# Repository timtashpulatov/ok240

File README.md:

# ok240

https://svofski.github.io/pretty-8080-assembler/?https://raw.githubusercontent.com/timtashpulatov/ok240/master/graf.asm

https://svofski.github.io/pretty-8080-assembler/?https://raw.githubusercontent.com/timtashpulatov/ok240/master/ints.asm

https://svofski.github.io/pretty-8080-assembler/?https://raw.githubusercontent.com/timtashpulatov/ok240/master/tet.asm

https://svofski.github.io/pretty-8080-assembler/?https://raw.githubusercontent.com/timtashpulatov/ok240/master/ark.asm

https://svofski.github.io/pretty-8080-assembler/?https://raw.githubusercontent.com/timtashpulatov/ok240/master/hexload.asm

Literature:

<ul>
<li>https://tetris.fandom.com/wiki/Random_Generator
<li>https://zx-pk.ru/threads/23100-generator-psevdosluchajnykh-chisel/page5.html
<li>https://tetris.fandom.com/wiki/Scoring
<li>https://en.wikipedia.org/wiki/Bit_blit
</ul>

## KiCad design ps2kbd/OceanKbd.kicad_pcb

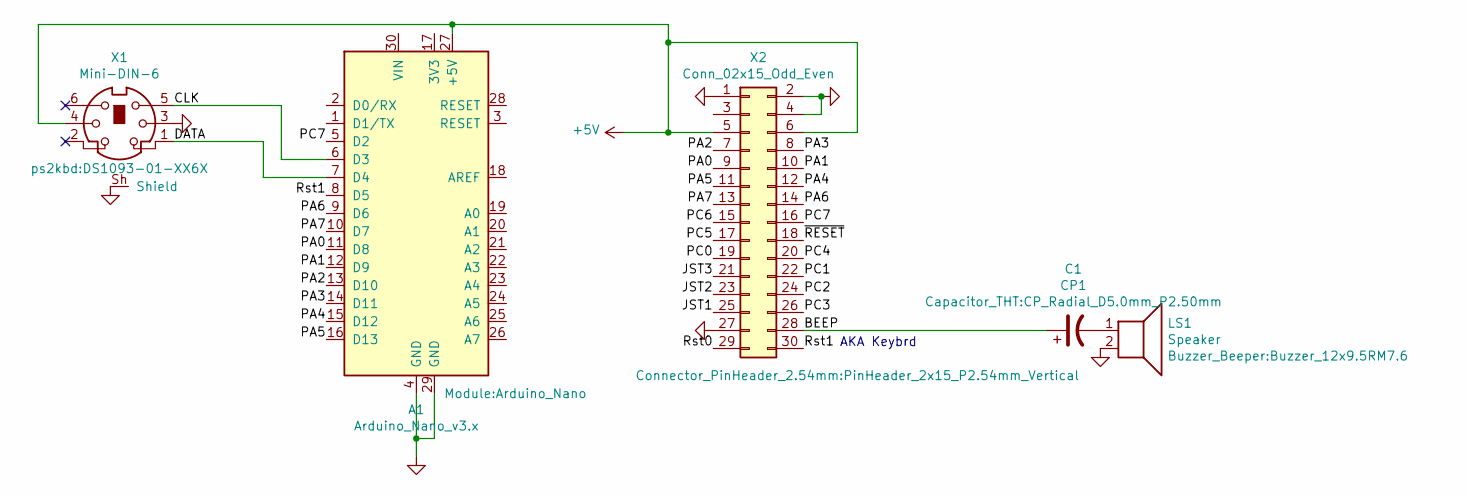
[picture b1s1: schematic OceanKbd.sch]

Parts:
A1: Arduino_Nano_v3.x; Arduino_Nano
C1: CP1; CP_Radial_D5.0mm_P2.50mm
LS1: Speaker; Buzzer_12x9.5RM7.6
X1: Mini-DIN-6; DS1093-01-XX6X
X2: Conn_02x15_Odd_Even; PinHeader_2x15_P2.54mm_Vertical

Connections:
+5V: A1.27 (+5V), X1.4, X2.5, X2.6
/BEEP: C1.1, X2.28
/CLK: A1.6 (D3), X1.5
/DATA: A1.7 (D4), X1.1
/JST1: X2.25
/JST2: X2.23
/JST3: X2.21
/PA0: A1.11 (D8), X2.9
/PA1: A1.12 (D9), X2.10
/PA2: A1.13 (D10), X2.7
/PA3: A1.14 (D11), X2.8
/PA4: A1.15 (D12), X2.12
/PA5: A1.16 (D13), X2.11
/PA6: A1.9 (D6), X2.14
/PA7: A1.10 (D7), X2.13
/PC0: X2.19
/PC1: X2.22
/PC2: X2.24
/PC3: X2.26
/PC4: X2.20
/PC5: X2.17
/PC6: X2.15
/PC7: A1.5 (D2), X2.16
/Rst0: X2.29
/Rst1: A1.8 (D5), X2.30
/~RESET: X2.18
GND: A1.4 (GND), A1.29 (GND), LS1.2, X1.3, X1.SH, X1.Sh (Shield), X2.1, X2.2, X2.4, X2.27
unnamed: C1.2, LS1.1

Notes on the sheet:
AKA Keybrd

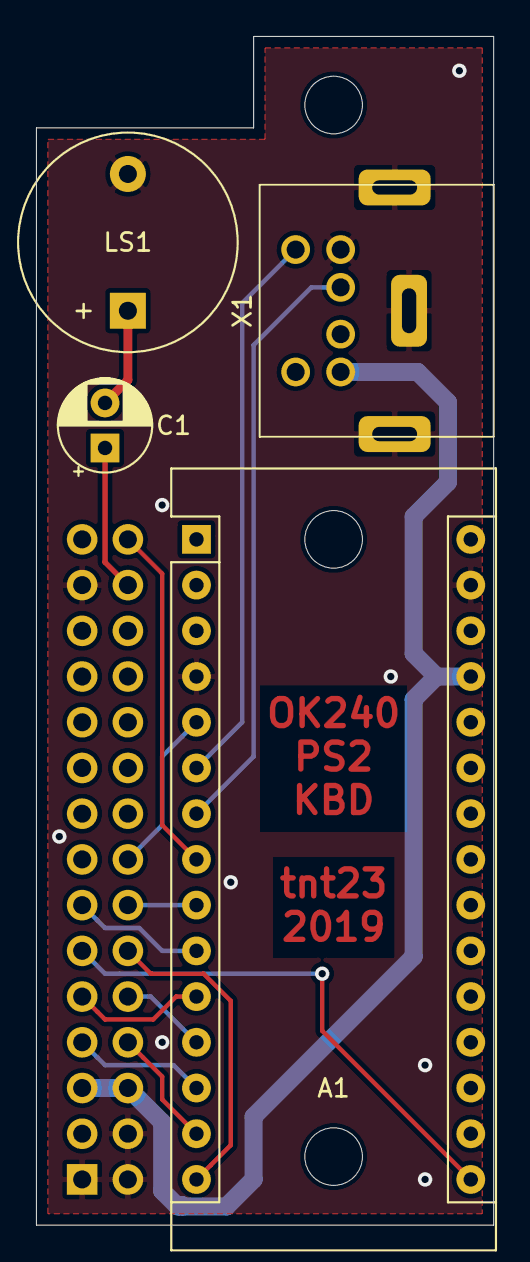
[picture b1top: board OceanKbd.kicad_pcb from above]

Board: 2 copper layers, 25.4 x 66.0 mm, 5 parts (1 on the bottom side), 16 nets.

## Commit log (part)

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2025-06-07 Add more cutouts to floppy frame
2025-06-08 More 3d stuff
2025-06-12 Another approach to bottom lid
2025-06-13 New top lid
2025-06-13 More Tops and drawings
2025-06-14 Update for top lid posts
2025-06-14 Add stringers to pillars
2025-06-18 Better Lid1 Part
2025-06-18 New BottomLid1
2025-06-18 More updates to bottom lid
2025-06-19 Simplified bottom with stands
2025-06-19 Redesign bottom and top halves
2025-06-20 Cleaned top and bottom lids
2025-06-20 Add floppy bracket
2025-06-20 Enhance side bracket with some chamfering
2025-06-21 Update side bracket, add mount posts to top lid
2025-06-21 Update assy
2025-06-27 Add lip to bottom lid
2025-06-27 PCB mount holes on lower lid
2025-07-01 Add floppy cutout
2025-07-02 New top and bottom parts with grooves
2025-07-11 Three locks added for bottom part
2025-07-12 Chamfer top alignment pads, add dowel pin for reference
2025-07-12 Use split halves as new Left and Right features
2025-07-12 Make lock pad two-dimentional and shift it for symmetry
2025-07-12 Add dowel holes to left half
2025-07-12 Shape dowel holes as drops for better printing and mirror them
2025-07-12 Teardrop dowel holes properly redone as features
2025-07-19 Add vents to Left bottom part
2025-07-20 Rename vents feature to Vents
2025-07-21 Add supporting lip
2025-07-22 Fix left vents
2025-07-25 Add 1mm chamfer to left bottom part, to reduce elephant foot etc
2025-07-25 Change bottom chamfer for 45 degrees, add 1mm fillets
2025-07-25 Add right angle IDC 30-pin connector 3D models
2025-07-25 Fix lip chamfer and fillets
2025-07-25 Add fillets to right bottom part
2025-07-26 Increase fillet radius to 1.5mm
2025-07-26 Increase fillet radius to 1.5mm for Left bottom part
2025-07-27 Add cutouts for power button and LED
2025-07-27 Up bottom part
2025-07-29 Add stand with heat insert for power switch
2025-07-29 Add right stand
2025-07-29 Power button
2025-07-29 Misc up
2025-08-01 Fix left heat insert pocket on Power switch mount
2025-08-01 Update Power switch mount with support
2025-08-01 Add Power button mount part to Assembly
2025-08-01 Add Keyboard cutouts, update PCB with connector models
2025-08-01 Add FDD model
2025-08-02 Add plug for Video and Kbd cutout, and screw mount for it
2025-08-02 Video and kbd slot screw mount done
2025-08-02 Clean up VideoKbd mount hierarchy
2025-08-02 Add left slot mount
2025-08-02 Add corner blocker
2025-08-02 More rear panel connectors
2025-08-04 Modify keyboard cutout
2025-08-04 Make combined cutout for Interface and Kbd
2025-08-05 Modify panel cutout ribs, clone panel
2025-08-05 Add DC 2.1mm M8 panel socket
2025-08-09 Update rear cutouts and panels
2025-08-09 Add recess to panels bottom
2025-08-09 Add latches and tooth for panel (experimental), add RCA socket for Tape interface
2025-08-10 Add latches (?)
2025-08-12 Hinges!
2025-08-13 Thicken hinges a bit
2025-08-15 Round internal edge of panels; add lots of locks and mounts to test
2025-08-15 PS2 cutout added
2025-08-15 Reshape DSub cutouts, update screw mount stand
2025-08-15 More screw mounts
2025-08-16 Add left and right screw mounts to Interface and Kbd panels
2025-08-16 Update panel screw mounts for 8mm self taping screws
2025-08-16 Vents for top lid
2025-08-16 Top vents complete
2025-08-19 Start slicing
2025-08-20 Slicing almost complete
2025-08-21 Update left and right slices, so far with rim gap
2025-08-21 Interface between left and right parts complete
2025-08-22 Add separate file for Top Right part
2025-08-23 Deepen screw hole on left Interface body mount
2025-08-23 Update floppy bezel with cutouts
2025-08-23 Welcome Top Left slice document, kinda release candidate for printing
2025-08-28 Latest update
2025-08-28 STL files
2025-09-16 Add PCGET utility w/screenshot
2025-09-16 Add link to Pretty 8080 Assembler for PCGET
2025-09-21 Update hexload.asm
    Use COMBUF and fillfcb0/setdisk internal CCP calls to process optional filename
2025-09-24 Update io.asm
    Remove OK240-specific call to 0E003h upon exit (prints hex from accumulator). Now the code should run on any CP/M version
2025-10-13 Update graf.asm
    Remove unnecessary prints, set .ORG to 100H
2025-10-14 Disk support
2025-10-14 Update graf.asm
    Clean FCB after file deletion, to reset record counters SECREC, RANREC etc
2025-10-15 Introduce offset for future screen layout
2025-10-16 Update graf.asm
    Refactor WorkBitmapPreview
2025-10-16 Draw lines using ESC
2025-10-17 Extend preview to 8x8 blocks
2025-10-17 Update graf.asm
    Fix preview drawing code
    Add interrupt cheer
2025-10-18 Blinking cursor
2025-10-20 Stabilize cursor blinking
2025-10-21 Grids
2025-10-21 Fix grid painting
2025-10-21 Add debug
2025-10-22 Add own font
2025-10-23 Print filename in color
2025-10-23 Help and pictograms
2025-10-23 Save 4 sectors (non-efficient way)
2025-10-23 Update scrolling
2025-10-23 Read 4 sectors, more eye candy
2025-10-23 Add Home key
2025-10-24 More icons
2025-10-25 Paint list of bitmaps more efficiently
2025-10-25 Place bitmaps in the beginning of binary
2025-10-25 Save and load all 8 sectors (each 128-byte sector stores 8 color squares))
2025-10-25 Fixed cycling through fore (F) and background (B) colors
2025-10-25 More blobs
2025-10-27 Fix fore/back color cycling
2025-10-29 Add hex font
2025-10-29 Hex dump WIP
2025-10-30 Add hex dump
2025-10-30 Fix silly bug with TempChar overwriting Clipboard
2025-10-30 Add (H)ex dump toggle (non-working yet)
2025-10-30 Keep cursor position during navigation
2025-10-30 Navigate to neighbor tiles
2025-10-30 Position cursor properly when navigating
2025-10-30 Make it startable from address 100h
2025-11-01 Finally figure out timings for palettes switching
2025-11-04 Background colors gradient
2025-11-12 Add PaintSectorMark
2025-11-14 Add side indicator
2025-11-14 Add continuous drill with VR synched delay
2025-11-15 Reset side when homing
2025-11-15 Do both sides in Track sectors read test
2025-11-15 Add CRC status bit
2025-11-15 Continuous drill uses the same sector paint code
2025-11-17 Add timers and tasks infrastructure
2025-11-19 Add good/bad track bitmap phases
2025-11-19 Tracks bitmap fill works
2025-11-19 Add Disk Scan menu
2025-11-19 Use SIDE when drawing Track gauge
2025-11-22 Center sector hex dump horizontally
2025-11-26 Add labels for tracks 00 and 79
2025-11-26 Add fancy logo
